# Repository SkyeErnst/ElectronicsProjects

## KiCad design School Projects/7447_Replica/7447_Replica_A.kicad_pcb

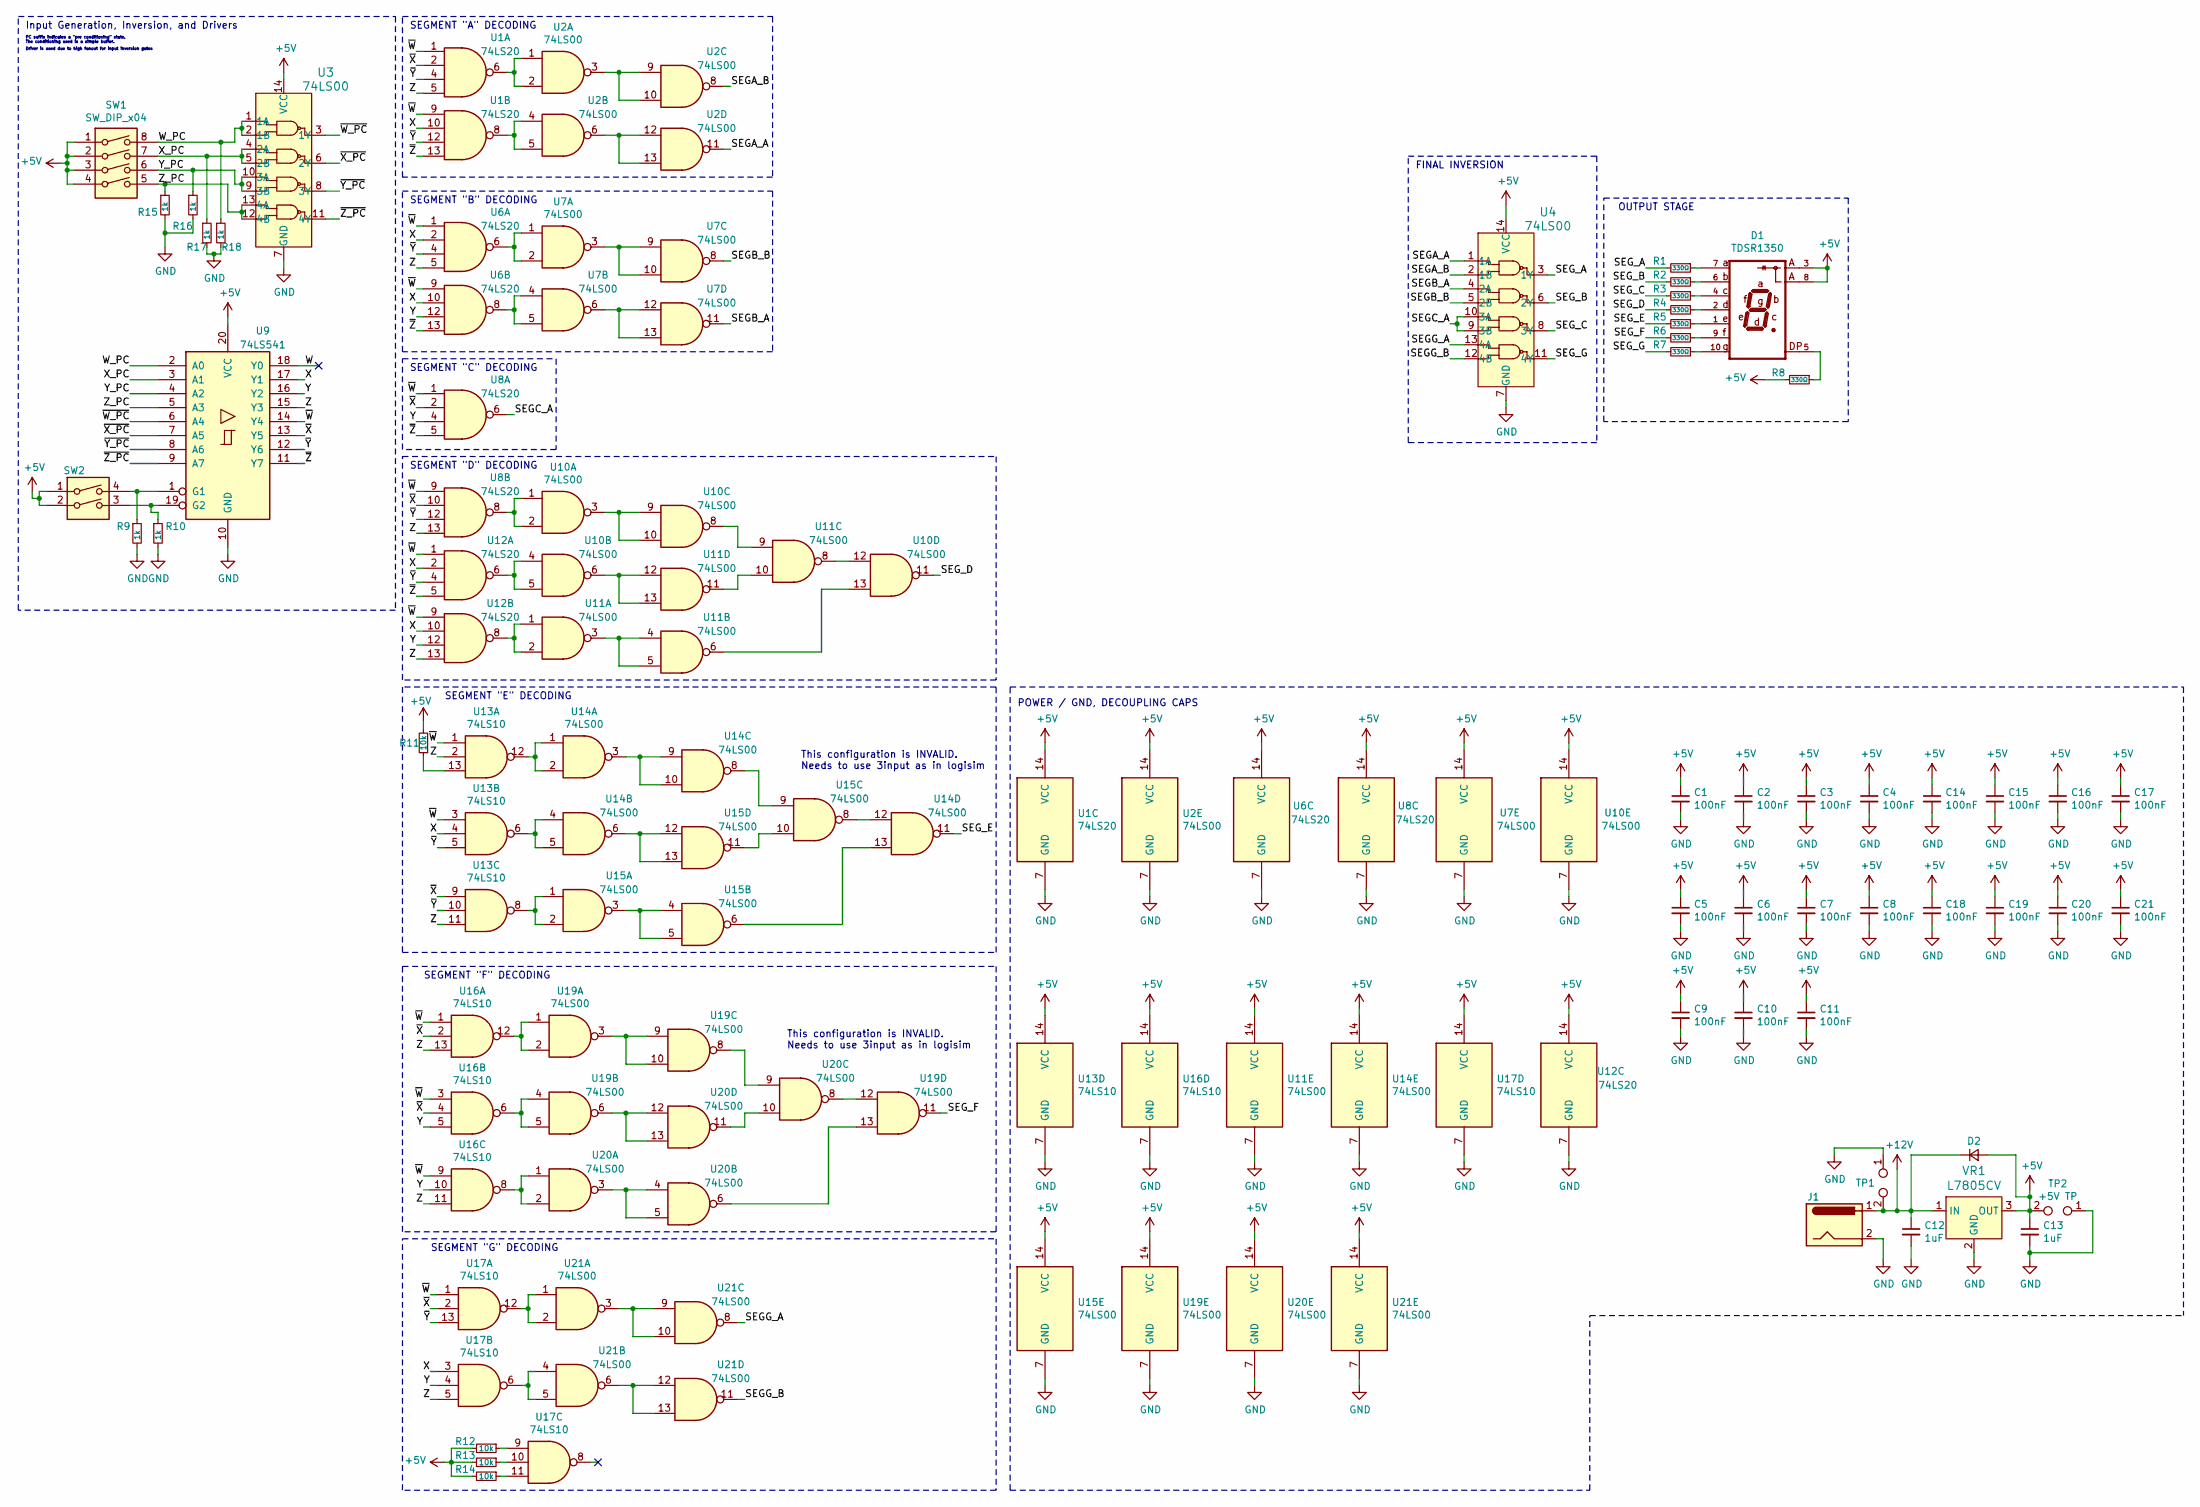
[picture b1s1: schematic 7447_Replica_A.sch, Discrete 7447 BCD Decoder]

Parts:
C1, C2, C3, C4, C5, C6, C7, C8, C9, C10, C11, C14, C15, C16, C17, C18, C19, C20, C21: 100nF; C_0805_2012Metric_Pad1.15x1.40mm_HandSolder
C12, C13: 1uF; C_0805_2012Metric_Pad1.15x1.40mm_HandSolder
D1: TDSR1350; DIPS1524W50P254L1240H710Q10; PARTREV 1.3
D2: D_Small; D_A-405_P10.16mm_Horizontal
J1: Barrel_Jack; BarrelJack_CUI_PJ-063AH_Horizontal
R1, R2, R3, R4, R5, R6, R7, R8: 330Ω; R_0805_2012Metric_Pad1.15x1.40mm_HandSolder
R9, R10, R15, R16, R17, R18: 1k; R_0805_2012Metric_Pad1.15x1.40mm_HandSolder
R11, R12, R13, R14: 10k; R_0805_2012Metric_Pad1.15x1.40mm_HandSolder
SW1: SW_DIP_x04; SW_DIP_SPSTx04_Slide_6.7x11.72mm_W7.62mm_P2.54mm_LowProfile
SW2: SW_DIP_x02; SW_DIP_SPSTx02_Slide_6.7x6.64mm_W7.62mm_P2.54mm_LowProfile
TP1: 12V TP; TestPoint_2Pads_Pitch5.08mm_Drill1.3mm
TP2: +5V TP; TestPoint_2Pads_Pitch5.08mm_Drill1.3mm
U1, U6, U8, U12: 74LS20; SOIC-14_3.9x8.7mm_P1.27mm
U2, U7, U10, U11, U14, U15, U19, U20, U21: 74LS00; SOIC-14_3.9x8.7mm_P1.27mm
U3, U4: 74LS00; SOIC-14_3.9x8.7mm_P1.27mm; MPN SN74LS00N; Digi-Key_PN 296-1626-ND
U9: 74LS541; DIP-20_W7.62mm_LongPads
U13, U16, U17: 74LS10; SOIC-14_3.9x8.7mm_P1.27mm
VR1: L7805CV; TO-220-3_Vertical; MPN L7805CV; Digi-Key_PN 497-1443-5-ND

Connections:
+5V: C1.1, C2.1, C3.1, C4.1, C5.1, C6.1, C7.1, C8.1, C9.1, C10.1, C11.1, C13.1, C14.1, C15.1, C16.1, C17.1, C18.1, C19.1, C20.1, C21.1, D1.3, D1.8, D2.2 (A), R8.2, R11.2, R12.2, R13.2, R14.2, SW1.1, SW1.2, SW1.3, SW1.4, SW2.1, SW2.2, TP2.2, U1.14 (VCC), U2.14 (VCC), U3.14 (VCC), U4.14 (VCC), U6.14 (VCC), U7.14 (VCC), U8.14 (VCC), U9.20 (VCC), U10.14 (VCC), U11.14 (VCC), U12.14 (VCC), U13.14 (VCC), U14.14 (VCC), U15.14 (VCC), U16.14 (VCC), U17.14 (VCC), U19.14 (VCC), U20.14 (VCC), U21.14 (VCC), VR1.3 (OUT)
+12V: C12.1, D2.1 (K), J1.1, TP1.2, VR1.1 (IN)
/SEGA_A: U2.11, U4.1 (1A)
/SEGA_B: U2.8, U4.2 (1B)
/SEGB_A: U4.4 (2A), U7.11
/SEGB_B: U4.5 (2B), U7.8
/SEGC_A: U4.9 (3B), U4.10 (3A), U8.6
/SEGG_A: U4.13 (4A), U21.8
/SEGG_B: U4.12 (4B), U21.11
/SEG_A: R1.2, U4.3 (1Y)
/SEG_B: R2.2, U4.6 (2Y)
/SEG_C: R3.2, U4.8 (3Y)
/SEG_D: R4.2, U10.11
/SEG_E: R5.2, U14.11
/SEG_F: R6.2, U19.11
/SEG_G: R7.2, U4.11 (4Y)
/W: U9.18 (Y0)
/W_PC: R18.1, SW1.8, U3.1 (1A), U3.2 (1B), U9.2 (A0)
/X: U1.10, U6.2, U6.10, U9.17 (Y1), U12.2, U12.10, U13.4, U17.3
/X_PC: R17.1, SW1.7, U3.4 (2A), U3.5 (2B), U9.3 (A1)
/Y: U6.12, U8.4, U9.16 (Y2), U12.12, U16.5, U16.10, U17.4
/Y_PC: R16.1, SW1.6, U3.9 (3B), U3.10 (3A), U9.4 (A2)
/Z: U1.5, U6.5, U8.13, U9.15 (Y3), U12.13, U13.2, U13.11, U16.11, U16.13, U17.5
/Z_PC: R15.1, SW1.5, U3.12 (4B), U3.13 (4A), U9.5 (A3)
/~W: U1.1, U1.9, U6.1, U6.9, U8.1, U8.9, U9.14 (Y4), U12.1, U12.9, U13.1, U13.3, U16.1, U16.3, U16.9, U17.1
/~W_PC: U3.3 (1Y), U9.6 (A4)
/~X: U1.2, U8.2, U8.10, U9.13 (Y5), U13.9, U16.2, U16.4, U17.2
/~X_PC: U3.6 (2Y), U9.7 (A5)
/~Y: U1.4, U1.12, U6.4, U8.12, U9.12 (Y6), U12.4, U13.5, U13.10, U17.13
/~Y_PC: U3.8 (3Y), U9.8 (A6)
/~Z: U1.13, U6.13, U8.5, U9.11 (Y7), U12.5
/~Z_PC: U3.11 (4Y), U9.9 (A7)
GND: C1.2, C2.2, C3.2, C4.2, C5.2, C6.2, C7.2, C8.2, C9.2, C10.2, C11.2, C12.2, C13.2, C14.2, C15.2, C16.2, C17.2, C18.2, C19.2, C20.2, C21.2, J1.2, R9.2, R10.2, R15.2, R16.2, R17.2, R18.2, TP1.1, TP2.1, U1.7 (GND), U2.7 (GND), U3.7 (GND), U4.7 (GND), U6.7 (GND), U7.7 (GND), U8.7 (GND), U9.10 (GND), U10.7 (GND), U11.7 (GND), U12.7 (GND), U13.7 (GND), U14.7 (GND), U15.7 (GND), U16.7 (GND), U17.7 (GND), U19.7 (GND), U20.7 (GND), U21.7 (GND), VR1.2 (GND)
unnamed: D1.1, R5.1
unnamed: D1.2, R4.1
unnamed: D1.4, R3.1
unnamed: D1.5, R8.1
unnamed: D1.6, R2.1
unnamed: D1.7, R1.1
unnamed: D1.9, R6.1
unnamed: D1.10, R7.1
unnamed: R9.1, SW2.4, U9.1 (G1)
unnamed: R10.1, SW2.3, U9.19 (G2)
unnamed: R11.1, U13.13
unnamed: R12.1, U17.9
unnamed: R13.1, U17.10
unnamed: R14.1, U17.11
unnamed: U1.6, U2.1, U2.2
unnamed: U1.8, U2.4, U2.5
unnamed: U2.3, U2.9, U2.10
unnamed: U2.6, U2.12, U2.13
unnamed: U6.6, U7.1, U7.2
unnamed: U6.8, U7.4, U7.5
unnamed: U7.3, U7.9, U7.10
unnamed: U7.6, U7.12, U7.13
unnamed: U8.8, U10.1, U10.2
unnamed: U10.4, U10.5, U12.6
unnamed: U10.6, U11.12, U11.13
unnamed: U10.8, U11.9
unnamed: U10.3, U10.9, U10.10
unnamed: U10.12, U11.8
unnamed: U10.13, U11.6
unnamed: U11.1, U11.2, U12.8
unnamed: U11.3, U11.4, U11.5
unnamed: U11.10, U11.11
unnamed: U13.6, U14.4, U14.5
unnamed: U13.8, U15.1, U15.2
unnamed: U13.12, U14.1, U14.2
unnamed: U14.6, U15.12, U15.13
unnamed: U14.8, U15.9
unnamed: U14.3, U14.9, U14.10
unnamed: U14.12, U15.8
unnamed: U14.13, U15.6
unnamed: U15.3, U15.4, U15.5
unnamed: U15.10, U15.11
unnamed: U16.6, U19.4, U19.5
unnamed: U16.8, U20.1, U20.2
unnamed: U16.12, U19.1, U19.2
unnamed: U17.6, U21.4, U21.5
unnamed: U17.12, U21.1, U21.2
unnamed: U19.6, U20.12, U20.13
unnamed: U19.8, U20.9
unnamed: U19.3, U19.9, U19.10
unnamed: U19.12, U20.8
unnamed: U19.13, U20.6
unnamed: U20.3, U20.4, U20.5
unnamed: U20.10, U20.11
unnamed: U21.3, U21.9, U21.10
unnamed: U21.6, U21.12, U21.13

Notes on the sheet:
Input Generation, Inversion, and Drivers
Driver is used due to high fanout for input inversion gates
PC suffix indicates a "pre conditioning" state. The conditioning used is a simple buffer.
POWER / GND, DECOUPLING CAPS
OUTPUT STAGE
FINAL INVERSION
SEGMENT "G" DECODING
SEGMENT "F" DECODING
SEGMENT "E" DECODING
SEGMENT "D" DECODING
SEGMENT "C" DECODING
SEGMENT "B" DECODING
SEGMENT "A" DECODING
This configuration is INVALID. Needs to use 3input as in logisim

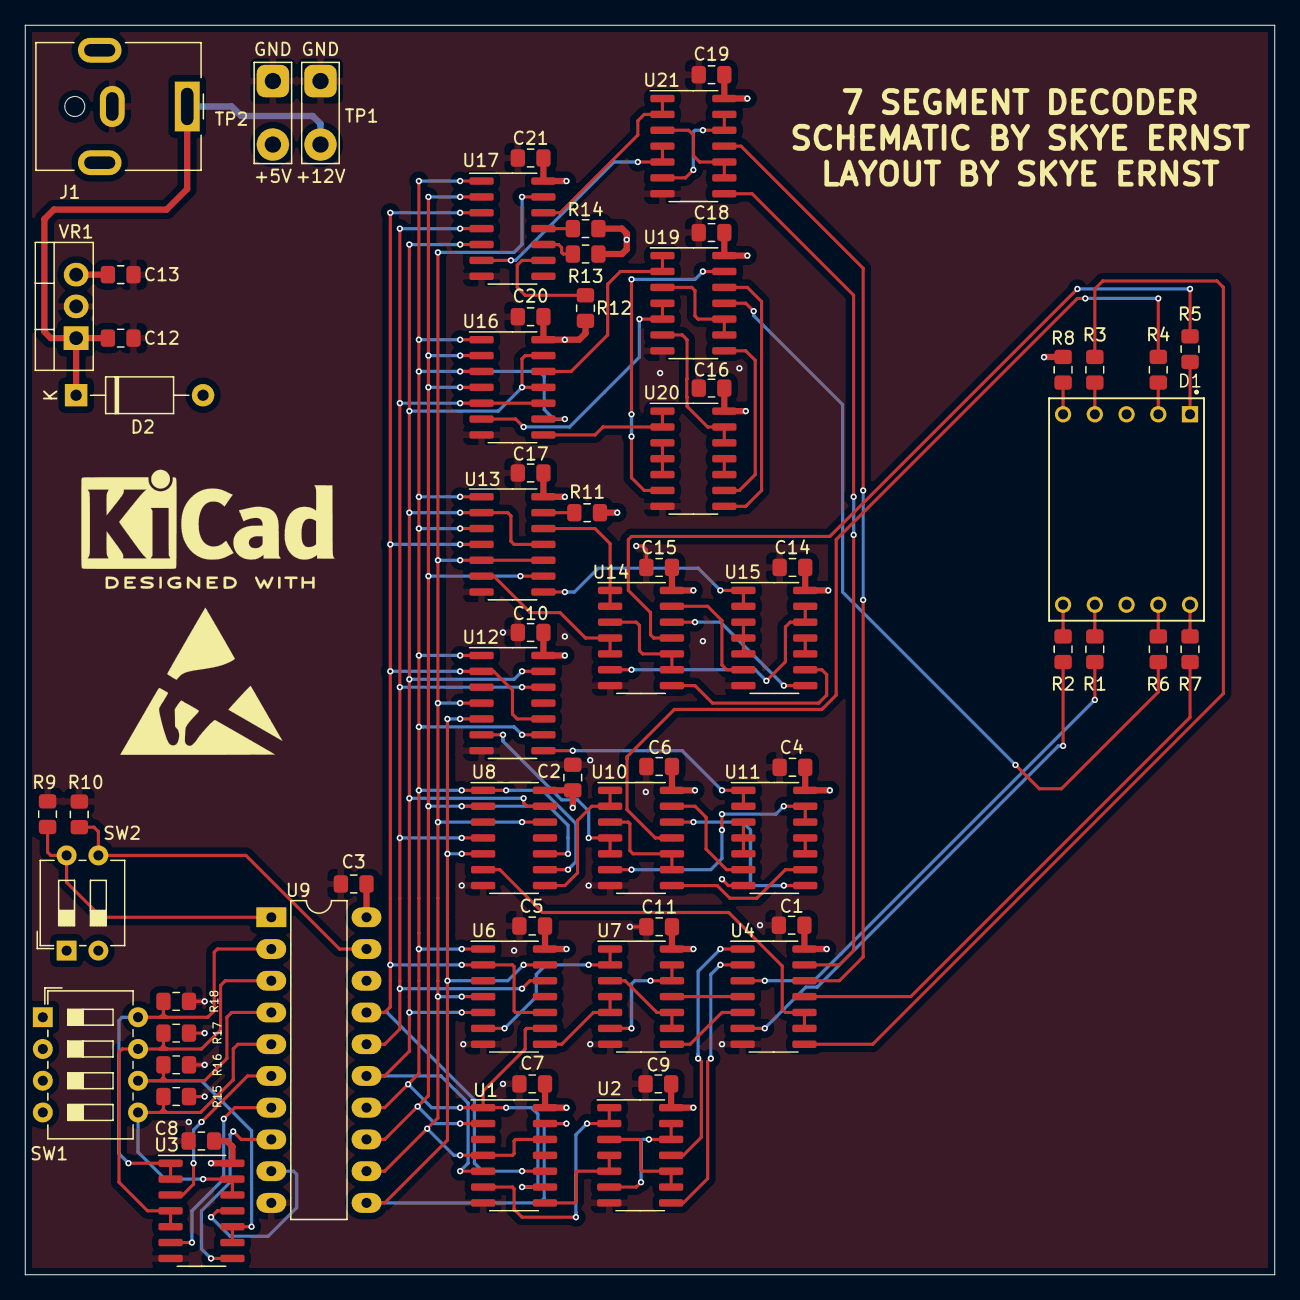
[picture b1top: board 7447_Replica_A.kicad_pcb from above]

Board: 4 copper layers, 100.0 x 100.0 mm, 66 parts (0 on the bottom side), 88 nets.

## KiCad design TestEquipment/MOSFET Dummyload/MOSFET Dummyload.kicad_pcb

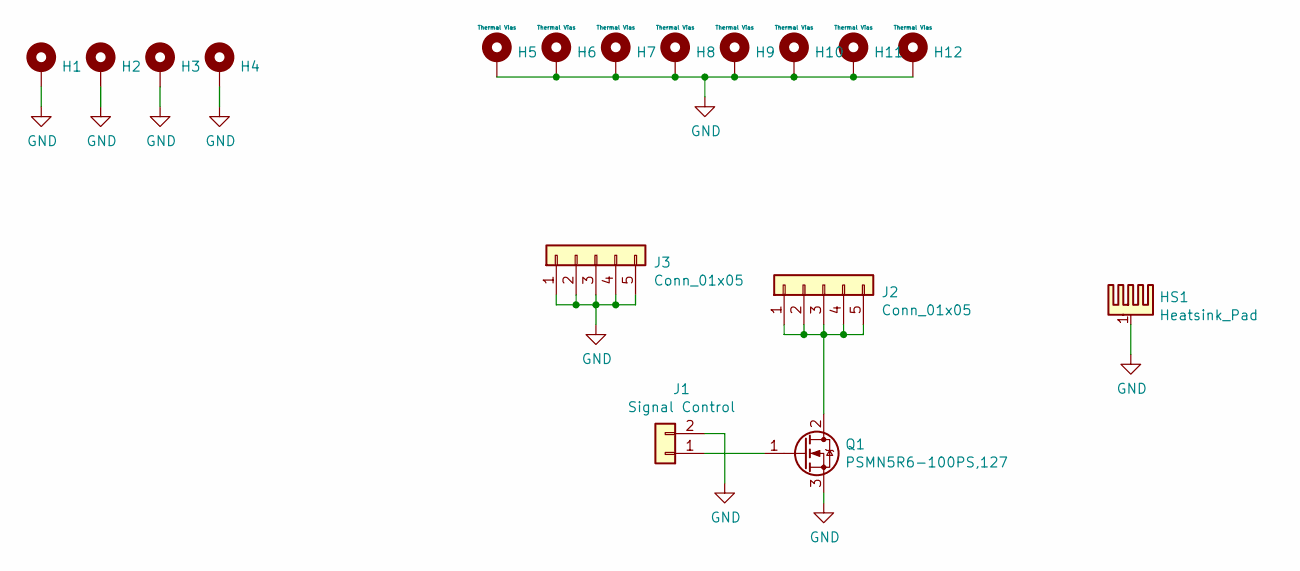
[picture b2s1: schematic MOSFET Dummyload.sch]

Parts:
H1, H2, H3, H4: MountingHole_Pad; 113 BK Mounting Hole
H5, H6, H7, H8, H9, H10, H11, H12: Thermal Vias; MountingHole_2.5mm_Pad_Via
HS1: Heatsink_Pad; VM1-038-1AE
J1: Signal Control; PinSocket_1x02_P2.54mm_Vertical
J2, J3: Conn_01x05; PinHeader_1x05_P2.54mm_Vertical
Q1: PSMN5R6-100PS,127; TO-220-3_Vertical

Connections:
GND: H1.1, H2.1, H3.1, H4.1, H5.1, H6.1, H7.1, H8.1, H9.1, H10.1, H11.1, H12.1, HS1.1, J1.2, J3.1, J3.2, J3.3, J3.4, J3.5, Q1.3 (S)
unnamed: J1.1, Q1.1 (G)
unnamed: J2.1, J2.2, J2.3, J2.4, J2.5, Q1.2 (D)

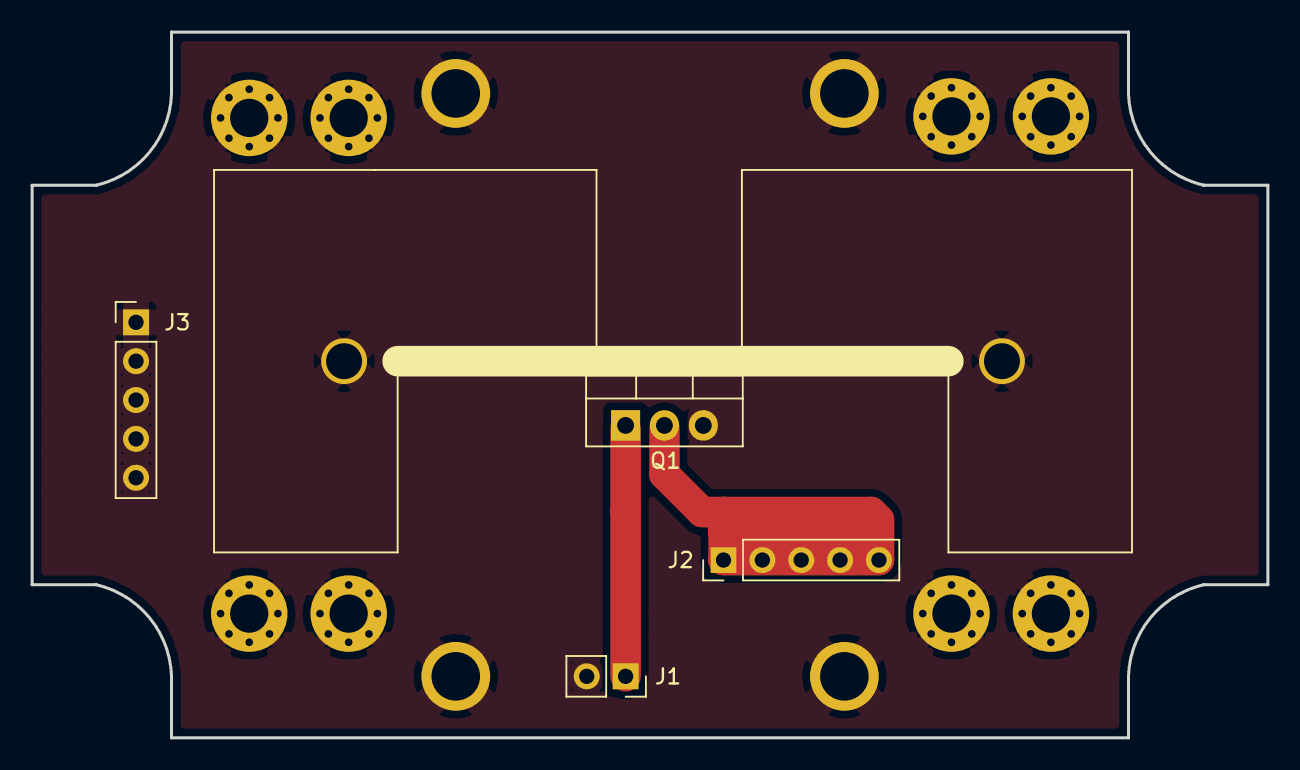
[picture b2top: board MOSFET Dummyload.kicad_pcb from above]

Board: 2 copper layers, 80.8 x 46.1 mm, 17 parts (0 on the bottom side), 3 nets.

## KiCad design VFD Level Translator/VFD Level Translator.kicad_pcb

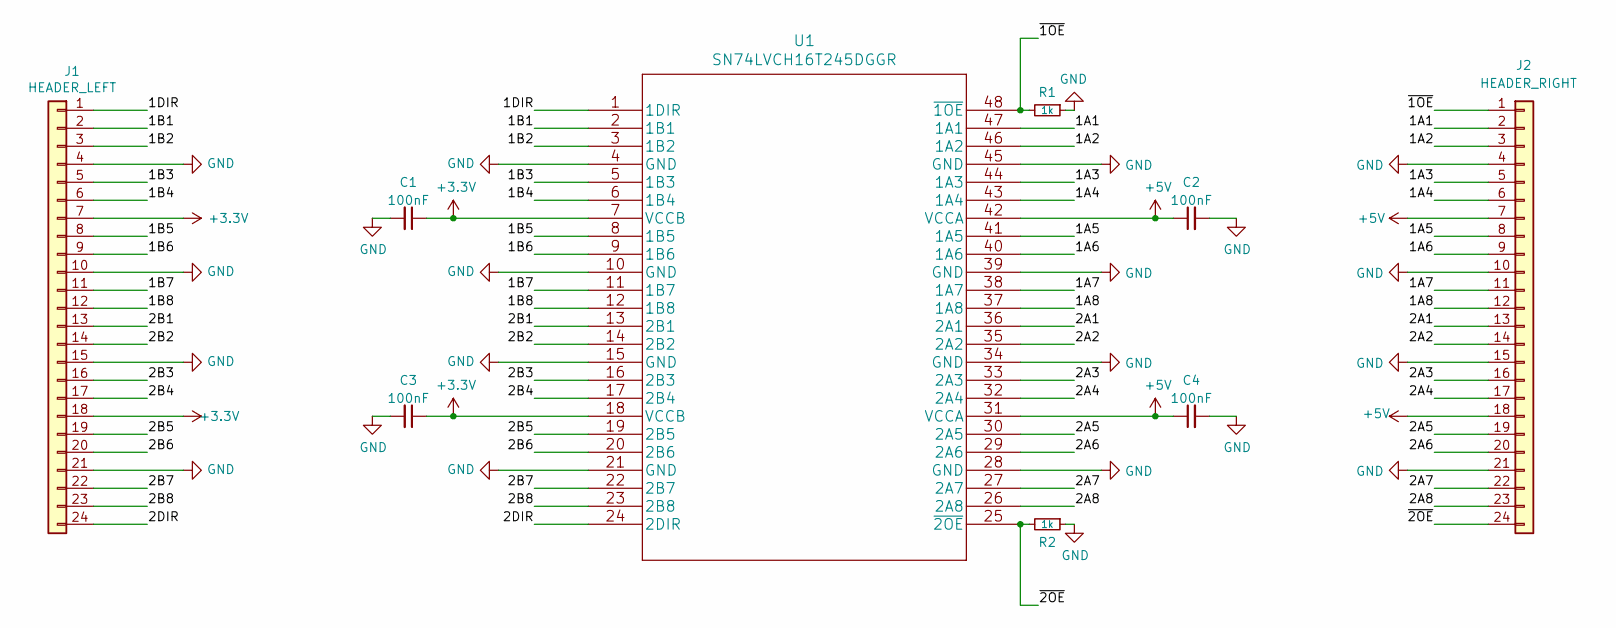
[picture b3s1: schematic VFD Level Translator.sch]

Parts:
C1, C2, C3, C4: 100nF; C_0805_2012Metric_Pad1.15x1.40mm_HandSolder
J1: HEADER_LEFT; PinHeader_1x24_P2.54mm_Vertical
J2: HEADER_RIGHT; PinHeader_1x24_P2.54mm_Vertical
R1, R2: 1k; R_0805_2012Metric_Pad1.15x1.40mm_HandSolder
U1: SN74LVCH16T245DGGR

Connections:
+3V3: C1.1, C3.1, J1.7, J1.18, U1.7 (VCCB), U1.18 (VCCB)
+5V: C2.1, C4.1, J2.7, J2.18, U1.31 (VCCA), U1.42 (VCCA)
/1A1: J2.2, U1.47 (1A1)
/1A2: J2.3, U1.46 (1A2)
/1A3: J2.5, U1.44 (1A3)
/1A4: J2.6, U1.43 (1A4)
/1A5: J2.8, U1.41 (1A5)
/1A6: J2.9, U1.40 (1A6)
/1A7: J2.11, U1.38 (1A7)
/1A8: J2.12, U1.37 (1A8)
/1B1: J1.2, U1.2 (1B1)
/1B2: J1.3, U1.3 (1B2)
/1B3: J1.5, U1.5 (1B3)
/1B4: J1.6, U1.6 (1B4)
/1B5: J1.8, U1.8 (1B5)
/1B6: J1.9, U1.9 (1B6)
/1B7: J1.11, U1.11 (1B7)
/1B8: J1.12, U1.12 (1B8)
/1DIR: J1.1, U1.1 (1DIR)
/2A1: J2.13, U1.36 (2A1)
/2A2: J2.14, U1.35 (2A2)
/2A3: J2.16, U1.33 (2A3)
/2A4: J2.17, U1.32 (2A4)
/2A5: J2.19, U1.30 (2A5)
/2A6: J2.20, U1.29 (2A6)
/2A7: J2.22, U1.27 (2A7)
/2A8: J2.23, U1.26 (2A8)
/2B1: J1.13, U1.13 (2B1)
/2B2: J1.14, U1.14 (2B2)
/2B3: J1.16, U1.16 (2B3)
/2B4: J1.17, U1.17 (2B4)
/2B5: J1.19, U1.19 (2B5)
/2B6: J1.20, U1.20 (2B6)
/2B7: J1.22, U1.22 (2B7)
/2B8: J1.23, U1.23 (2B8)
/2DIR: J1.24, U1.24 (2DIR)
/~1OE: J2.1, R1.2, U1.48 (~1OE)
/~2OE: J2.24, R2.2, U1.25 (~2OE)
GND: C1.2, C2.2, C3.2, C4.2, J1.4, J1.10, J1.15, J1.21, J2.4, J2.10, J2.15, J2.21, R1.1, R2.1, U1.4 (GND), U1.10 (GND), U1.15 (GND), U1.21 (GND), U1.28 (GND), U1.34 (GND), U1.39 (GND), U1.45 (GND)

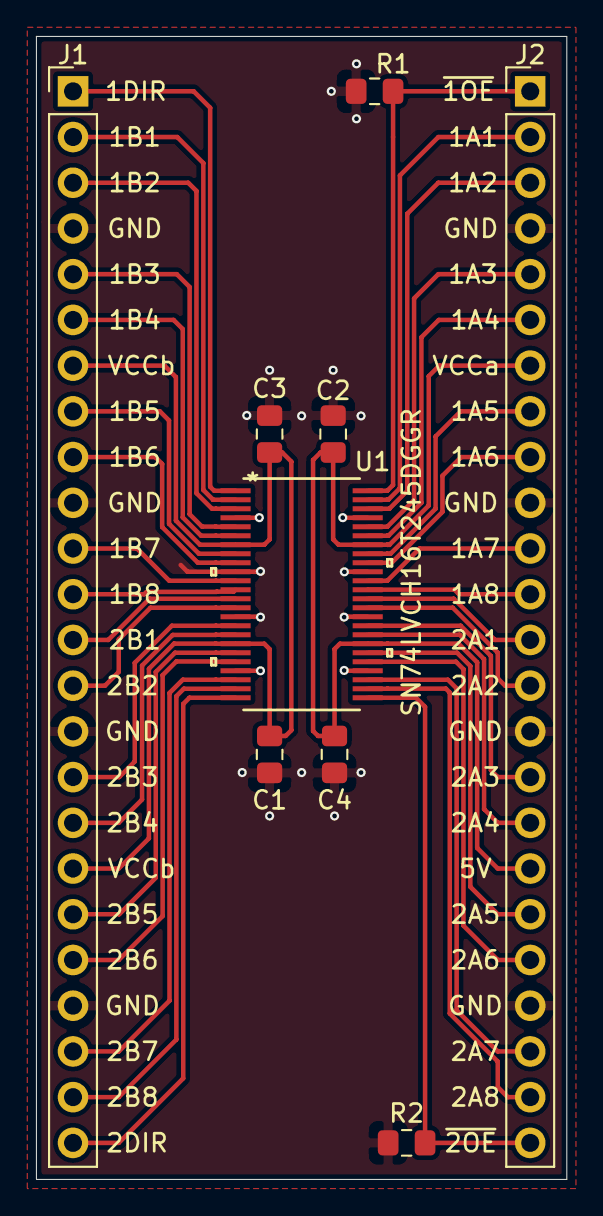
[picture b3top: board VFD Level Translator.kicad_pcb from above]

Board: 2 copper layers, 29.5 x 63.5 mm, 9 parts (0 on the bottom side), 39 nets.

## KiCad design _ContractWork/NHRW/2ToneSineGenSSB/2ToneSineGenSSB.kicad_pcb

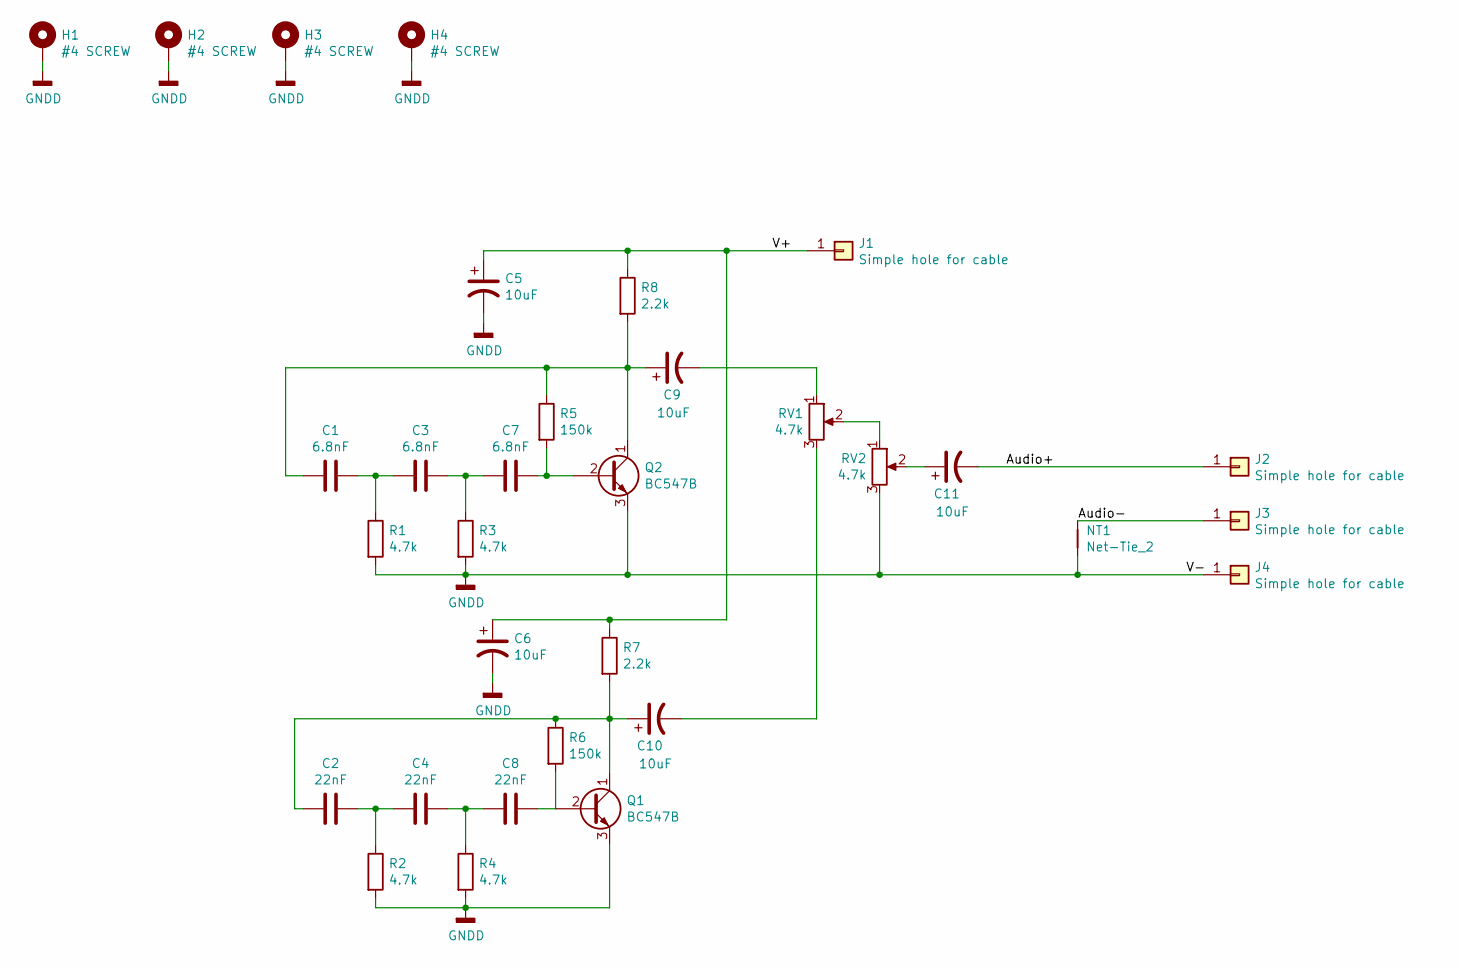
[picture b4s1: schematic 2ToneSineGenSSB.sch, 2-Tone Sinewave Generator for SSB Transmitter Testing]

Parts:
C1, C3, C7: 6.8nF; QYX1H682JTP
C2, C4, C8: 22nF; C_Disc_D7.5mm_W2.5mm_P5.00mm
C5, C6, C9, C10, C11: 10uF; CP_Radial_D5.0mm_P2.50mm
H1, H2, H3, H4: #4 SCREW; 1591XXAFL Mounting Hole
J1, J2, J3, J4: Simple hole for cable; SolderWirePad_1x01_Drill1mm
NT1: Net-Tie_2; NetTie-2_SMD_Pad0.5mm
Q1, Q2: BC547B; TO-92
R1, R2, R3, R4: 4.7k; R_Axial_DIN0309_L9.0mm_D3.2mm_P15.24mm_Horizontal
R5, R6: 150k; R_Axial_DIN0309_L9.0mm_D3.2mm_P15.24mm_Horizontal
R7, R8: 2.2k; R_Axial_DIN0309_L9.0mm_D3.2mm_P15.24mm_Horizontal
RV1, RV2: 4.7k; Potentiometer_Bourns_3266W_Vertical

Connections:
/Audio+: C11.2, J2.1
/Audio-: J3.1, NT1.1
/V+: C5.1, C6.1, J1.1, R7.1, R8.1
GNDD: C5.2, C6.2, H1.1, H2.1, H3.1, H4.1, J4.1, NT1.2, Q1.3 (E), Q2.3 (E), R1.2, R2.2, R3.2, R4.2, RV2.3
unnamed: C1.1, C3.2, R1.1
unnamed: C1.2, C9.1, Q2.1 (C), R5.1, R8.2
unnamed: C2.1, C4.2, R2.1
unnamed: C3.1, C7.2, R3.1
unnamed: C4.1, C8.2, R4.1
unnamed: C7.1, Q2.2 (B), R5.2
unnamed: C8.1, Q1.2 (B), R6.2
unnamed: C9.2, RV1.1
unnamed: C2.2, C10.1, Q1.1 (C), R6.1, R7.2
unnamed: C10.2, RV1.3
unnamed: C11.1, RV2.2
unnamed: RV1.2, RV2.1

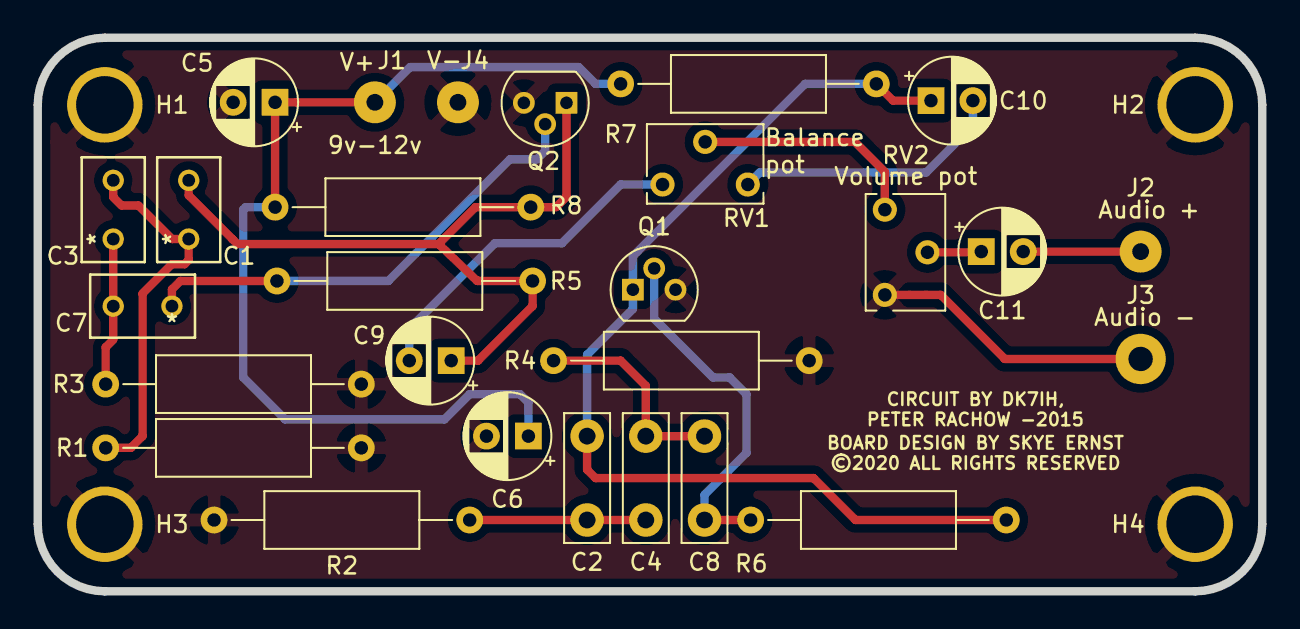
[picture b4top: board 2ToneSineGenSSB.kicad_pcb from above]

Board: 2 copper layers, 73.0 x 33.0 mm, 32 parts (0 on the bottom side), 16 nets.

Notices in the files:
_ContractWork/NHRW/2ToneSineGenSSB/2ToneSineGenSSB.kicad_pcb:
©2020 ALL RIGHTS RESERVED
parts and their libraries:
Copyright 2016 Accelerated Designs. All rights reserved.
